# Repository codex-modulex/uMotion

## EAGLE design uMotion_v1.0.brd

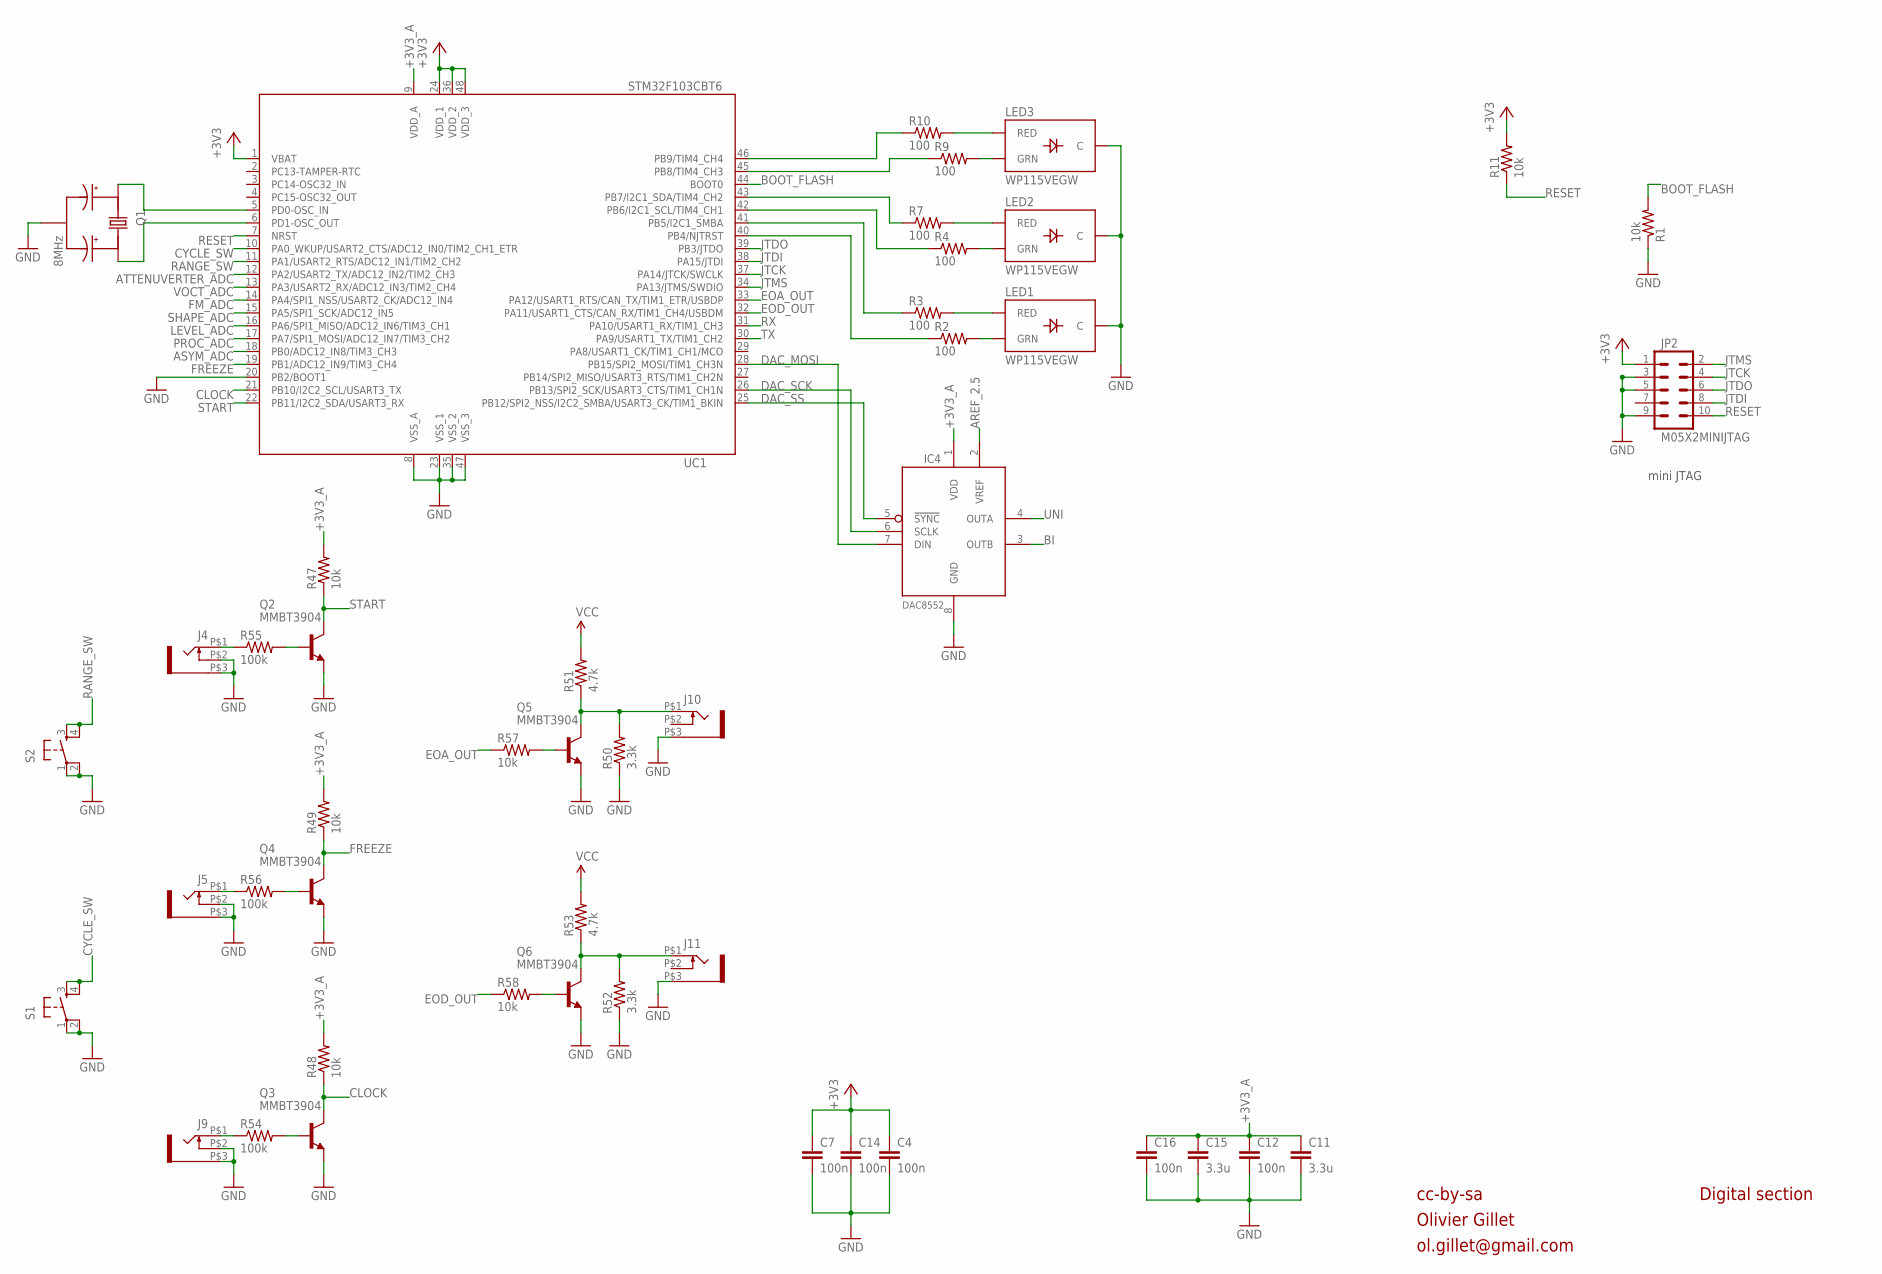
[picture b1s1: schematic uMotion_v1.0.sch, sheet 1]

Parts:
C4, C7, C12, C14, C16: 100n; PARTS_AMAN_RESISTOR_0603
C11, C15: 3.3u; PARTS_AMAN_RESISTOR_0603
IC4: DAC8552; MSOP-8
J4, J5, J9, J10, J11: WQP-PJ301M-12_JACK
JP2: M05X2MINIJTAG; 2X5-1.27
LED1, LED2, LED3: WP115VEGW; LED-BICOLOR-THROUGHHOLE
Q1: 8MHz; INSTRUO_CRYSTAL_SMALLER
Q2, Q3, Q4, Q5, Q6: MMBT3904; SOT23-BEC
R1, R11, R47, R48, R49, R57, R58: 10k; PARTS_AMAN_RESISTOR_0603
R2, R3, R4, R7, R9, R10: 100; PARTS_AMAN_RESISTOR_0603
R50, R52: 3.3k; PARTS_AMAN_RESISTOR_0603
R51, R53: 4.7k; PARTS_AMAN_RESISTOR_0603
R54, R55, R56: 100k; PARTS_AMAN_RESISTOR_0603
S1, S2: TAC_SWITCHPTH; TACTILE-PTH
UC1: STM32F103CBT6; LQFP48

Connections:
+3V3: C4.1, C7.1, C14.1, JP2.1, R11.2, UC1.1 (VBAT), UC1.24 (VDD_1), UC1.36 (VDD_2), UC1.48 (VDD_3); also elsewhere on the board
+3V3_A: C11.1, C12.1, C15.1, C16.1, IC4.1 (VDD), R47.2, R48.2, R49.2, UC1.9 (VDD_A); also elsewhere on the board
AREF_2.5: IC4.2 (VREF); also elsewhere on the board
ASYM_ADC: UC1.18 (PB0/ADC12_IN8/TIM3_CH3); also elsewhere on the board
ATTENUVERTER_ADC: UC1.12 (PA2/USART2_TX/ADC12_IN2/TIM2_CH3); also elsewhere on the board
BI: IC4.3 (OUTB); also elsewhere on the board
BOOT_FLASH: R1.2, UC1.44 (BOOT0)
CLOCK: Q3.C, R48.1, UC1.21 (PB10/I2C2_SCL/USART3_TX)
CYCLE_SW: S1.3, S1.4, UC1.10 (PA0_WKUP/USART2_CTS/ADC12_IN0/TIM2_CH1_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)
DAC_MOSI: IC4.7 (DIN), UC1.28 (PB15/SPI2_MOSI/TIM1_CH3N)
DAC_SCK: IC4.6 (SCLK), UC1.26 (PB13/SPI2_SCK/USART3_CTS/TIM1_CH1N)
DAC_SS: IC4.5 (!SYNC), UC1.25 (PB12/SPI2_NSS/I2C2_SMBA/USART3_CK/TIM1_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)
EOA_OUT: R57.1, UC1.33 (PA12/USART1_RTS/CAN_TX/TIM1_ETR/USBDP)
EOD_OUT: R58.1, UC1.32 (PA11/USART1_CTS/CAN_RX/TIM1_CH4/USBDM)
FM_ADC: UC1.14 (PA4/SPI1_NSS/USART2_CK/ADC12_IN4); also elsewhere on the board
FREEZE: Q4.C, R49.1, UC1.19 (PB1/ADC12_IN9/TIM3_CH4)
GND: C4.2, C7.2, C11.2, C12.2, C14.2, C15.2, C16.2, IC4.8 (GND), J4.P$2 (3), J4.P$3 (1), J5.P$2 (3), J5.P$3 (1), J9.P$2 (3), J9.P$3 (1), J10.P$3 (1), J11.P$3 (1), JP2.3, JP2.5, JP2.9, LED1.2 (C), LED2.2 (C), LED3.2 (C), Q1.GND, Q2.E, Q3.E, Q4.E, Q5.E, Q6.E, R1.1, R50.1, R52.1, S1.1, S1.2, S2.1, S2.2, UC1.8 (VSS_A), UC1.20 (PB2/BOOT1), UC1.23 (VSS_1), UC1.35 (VSS_2), UC1.47 (VSS_3); also elsewhere on the board
JTCK: JP2.4, UC1.37 (PA14/JTCK/SWCLK)
JTDI: JP2.8, UC1.38 (PA15/JTDI)
JTDO: JP2.6, UC1.39 (PB3/JTDO)
JTMS: JP2.2, UC1.34 (PA13/JTMS/SWDIO)
LEVEL_ADC: UC1.16 (PA6/SPI1_MISO/ADC12_IN6/TIM3_CH1); also elsewhere on the board
unnamed: Q1.X2, UC1.6 (PD1-OSC_OUT)
unnamed: Q1.X1, UC1.5 (PD0-OSC_IN)
unnamed: J5.P$1 (2), R56.1
unnamed: Q4.B, R56.2
unnamed: J9.P$1 (2), R54.1
unnamed: Q3.B, R54.2
unnamed: Q6.B, R58.2
unnamed: J11.P$1 (2), Q6.C, R52.2, R53.1
unnamed: LED3.3 (RED), R10.2
unnamed: LED3.1 (GRN), R9.2
unnamed: LED2.3 (RED), R7.2
unnamed: LED2.1 (GRN), R4.2
unnamed: LED1.3 (RED), R3.2
unnamed: LED1.1 (GRN), R2.2
unnamed: R10.1, UC1.46 (PB9/TIM4_CH4)
unnamed: R9.1, UC1.45 (PB8/TIM4_CH3)
unnamed: R7.1, UC1.43 (PB7/I2C1_SDA/TIM4_CH2)
unnamed: R4.1, UC1.42 (PB6/I2C1_SCL/TIM4_CH1)
unnamed: R3.1, UC1.41 (PB5/I2C1_SMBA)
unnamed: R2.1, UC1.40 (PB4/NJTRST)
unnamed: J10.P$1 (2), Q5.C, R50.2, R51.1
unnamed: Q5.B, R57.2
unnamed: J4.P$1 (2), R55.1
unnamed: Q2.B, R55.2
PROC_ADC: UC1.17 (PA7/SPI1_MOSI/ADC12_IN7/TIM3_CH2); also elsewhere on the board
RANGE_SW: S2.3, S2.4, UC1.11 (PA1/USART2_RTS/ADC12_IN1/TIM2_CH2)
RESET: JP2.10, R11.1, UC1.7 (NRST)
RX: UC1.31 (PA10/USART1_RX/TIM1_CH3)
SHAPE_ADC: UC1.15 (PA5/SPI1_SCK/ADC12_IN5); also elsewhere on the board
START: Q2.C, R47.1, UC1.22 (PB11/I2C2_SDA/USART3_RX)
TX: UC1.30 (PA9/USART1_TX/TIM1_CH2)
UNI: IC4.4 (OUTA); also elsewhere on the board
VCC: R51.2, R53.2; also elsewhere on the board
VOCT_ADC: UC1.13 (PA3/USART2_RX/ADC12_IN3/TIM2_CH4); also elsewhere on the board

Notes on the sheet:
cc-by-sa
Olivier Gillet
ol.gillet@gmail.com
Digital section
mini JTAG

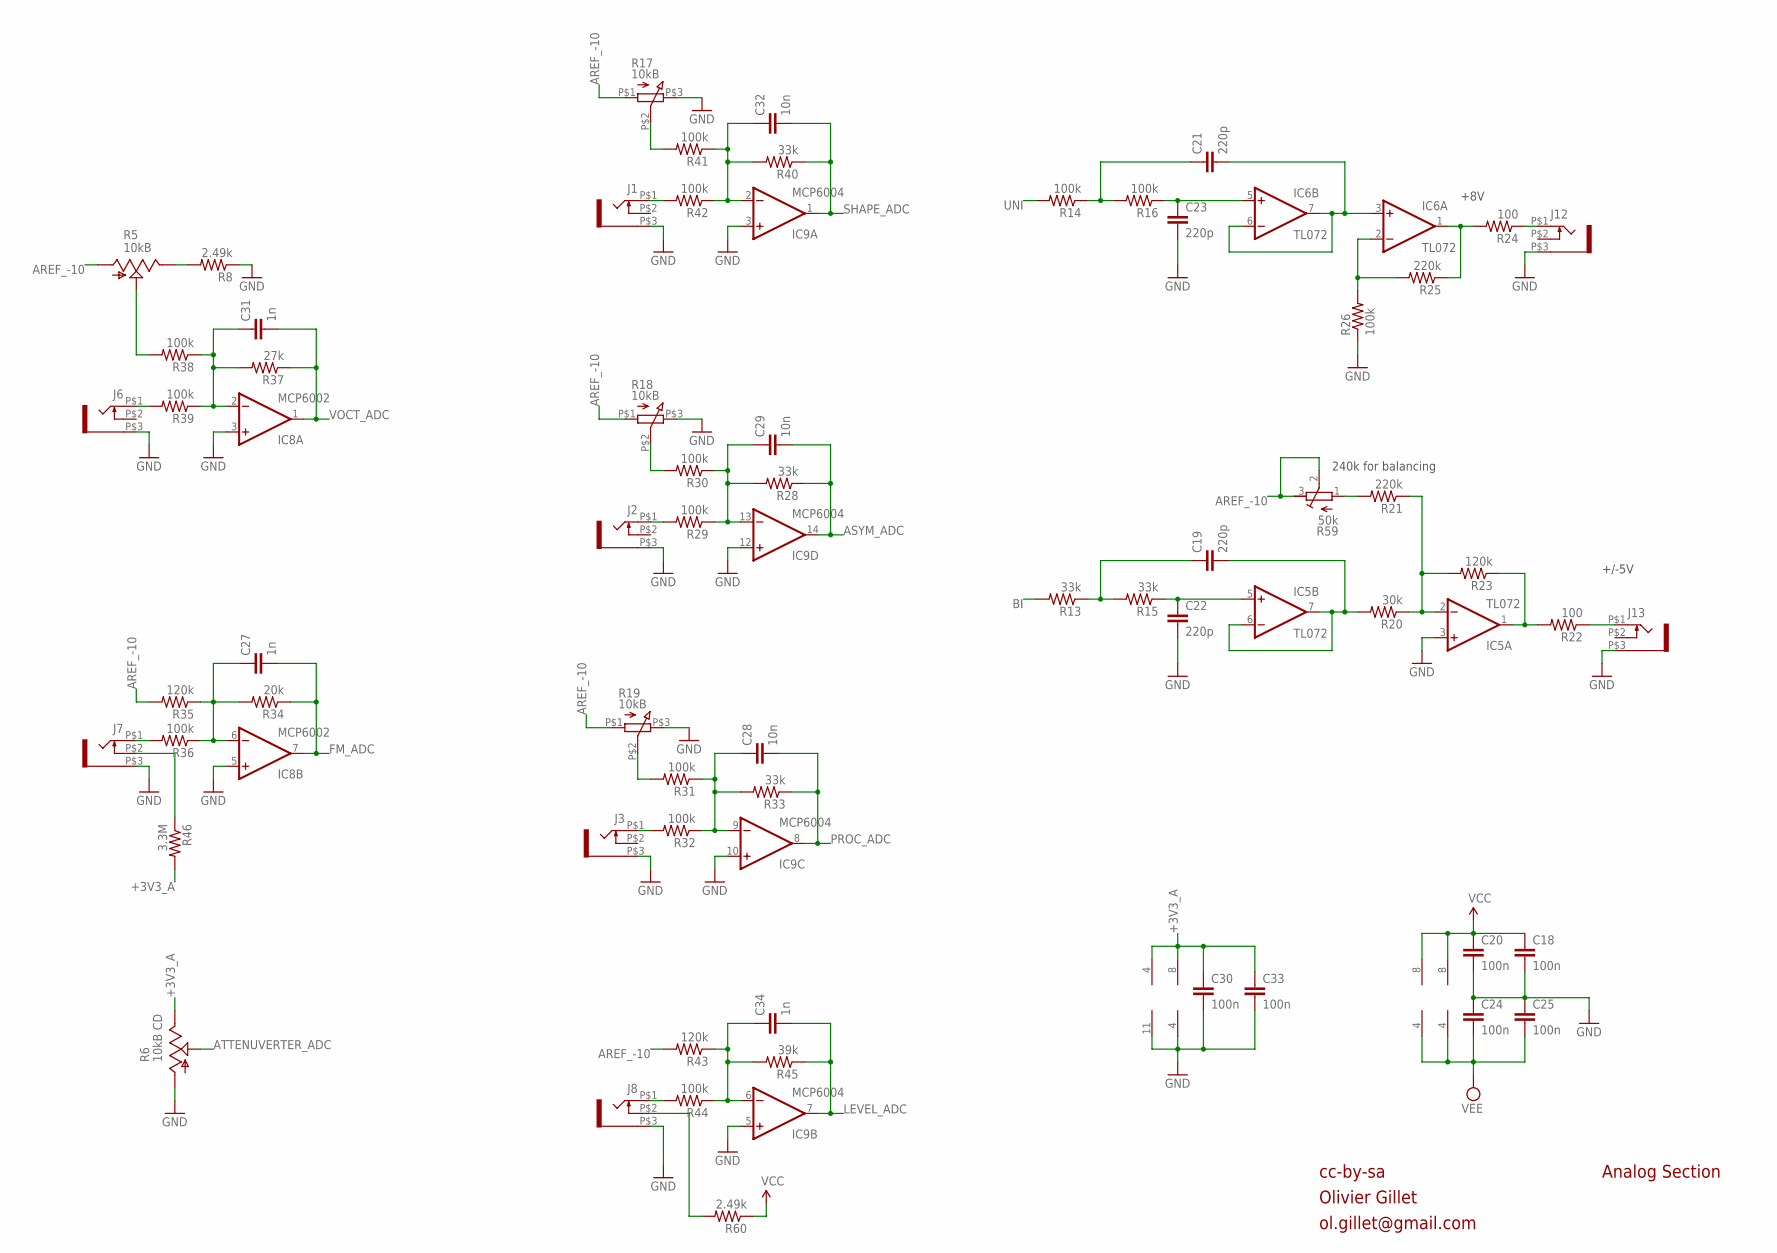
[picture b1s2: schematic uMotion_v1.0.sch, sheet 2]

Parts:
C18, C20, C24, C25, C30, C33: 100n; PARTS_AMAN_RESISTOR_0603
C19, C21, C22, C23: 220p; PARTS_AMAN_RESISTOR_0603
C27, C31, C34: 1n; PARTS_AMAN_RESISTOR_0603
C28, C29, C32: 10n; PARTS_AMAN_RESISTOR_0603
IC5, IC6: TL072; SO08
IC8: MCP6002; SO08
IC9: MCP6004; SO14
J1, J2, J3, J6, J7, J8, J12, J13: WQP-PJ301M-12_JACK
R5: 10kB; ALPS_POT_VERTICAL_PS
R6: 10kB CD; ALPS_POT_VERTICAL_PS
R8: 2.49k; PARTS_AMAN_RESISTOR_0603
R13, R15, R28, R33, R40: 33k; PARTS_AMAN_RESISTOR_0603
R14, R16, R26, R29, R30, R31, R32, R36, R38, R39, R41, R42, R44: 100k; PARTS_AMAN_RESISTOR_0603
R17, R18, R19: 10kB; INSTRUO_Q-POT2
R20: 30k; PARTS_AMAN_RESISTOR_0603
R21, R25: 220k; PARTS_AMAN_RESISTOR_0603
R22, R24: 100; PARTS_AMAN_RESISTOR_0603
R23, R35, R43: 120k; PARTS_AMAN_RESISTOR_0603
R34: 20k; PARTS_AMAN_RESISTOR_0603
R37: 27k; PARTS_AMAN_RESISTOR_0603
R45: 39k; PARTS_AMAN_RESISTOR_0603
R46: 3.3M; PARTS_AMAN_RESISTOR_0603
R59: 50k; RTRIM3296X
R60: 2.49k; R0805

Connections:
+3V3_A: C30.1, C33.1, IC8.8 (V+), IC9.4 (V+), R6.P$1 (E), R46.2; also elsewhere on the board
AREF_-10: R5.P$3 (A), R17.P$1 (1), R18.P$1 (1), R19.P$1 (1), R35.2, R43.2, R59.2 (S), R59.3 (A); also elsewhere on the board
ASYM_ADC: C29.2, IC9.14 (OUT), R28.1; also elsewhere on the board
ATTENUVERTER_ADC: R6.P$2 (S); also elsewhere on the board
BI: R13.2; also elsewhere on the board
BI_OUT: IC5.1 (OUT), R22.2, R23.1
FM_ADC: C27.2, IC8.7 (OUT), R34.1; also elsewhere on the board
F_CV: IC5.2 (-IN), R20.1, R21.1, R23.2
GND: C18.2, C20.2, C22.2, C23.2, C24.1, C25.1, C30.2, C33.2, IC5.3 (+IN), IC8.3 (+IN), IC8.4 (V-), IC8.5 (+IN), IC9.3 (+IN), IC9.5 (+IN), IC9.10 (+IN), IC9.11 (V-), IC9.12 (+IN), J1.P$3 (1), J2.P$3 (1), J3.P$3 (1), J6.P$3 (1), J7.P$3 (1), J8.P$3 (1), J12.P$3 (1), J13.P$3 (1), R6.P$3 (A), R8.1, R17.P$3 (3), R18.P$3 (3), R19.P$3 (3), R26.1; also elsewhere on the board
LEVEL_ADC: C34.2, IC9.7 (OUT), R45.1; also elsewhere on the board
unnamed: J1.P$1 (2), R42.2
unnamed: C32.1, IC9.2 (-IN), R40.2, R41.1, R42.1
unnamed: R17.P$2 (2), R41.2
unnamed: J2.P$1 (2), R29.2
unnamed: C29.1, IC9.13 (-IN), R28.2, R29.1, R30.1
unnamed: J7.P$2 (3), R46.1
unnamed: R18.P$2 (2), R30.2
unnamed: J3.P$1 (2), R32.2
unnamed: C28.1, IC9.9 (-IN), R31.1, R32.1, R33.2
unnamed: R19.P$2 (2), R31.2
unnamed: J8.P$1 (2), R44.2
unnamed: C34.1, IC9.6 (-IN), R43.1, R44.1, R45.2
unnamed: J6.P$1 (2), R39.2
unnamed: C31.1, IC8.2 (-IN), R37.2, R38.1, R39.1
unnamed: R5.P$2 (S), R38.2
unnamed: J13.P$1 (2), R22.1
unnamed: R5.P$1 (E), R8.2
unnamed: J7.P$1 (2), R36.2
unnamed: C27.1, IC8.6 (-IN), R34.2, R35.1, R36.1
unnamed: R21.2, R59.1 (E)
unnamed: IC6.2 (-IN), R25.2, R26.2
unnamed: C19.2, IC5.6 (-IN), IC5.7 (OUT), R20.2
unnamed: C22.1, IC5.5 (+IN), R15.1
unnamed: C19.1, R13.1, R15.2
unnamed: IC6.1 (OUT), R24.2, R25.1
unnamed: J8.P$2 (3), R60.2
unnamed: C21.2, IC6.3 (+IN), IC6.6 (-IN), IC6.7 (OUT)
unnamed: C23.1, IC6.5 (+IN), R16.1
unnamed: C21.1, R14.1, R16.2
PROC_ADC: C28.2, IC9.8 (OUT), R33.1; also elsewhere on the board
SHAPE_ADC: C32.2, IC9.1 (OUT), R40.1; also elsewhere on the board
UNI: R14.2; also elsewhere on the board
UNI_OUT: J12.P$1 (2), R24.1
VCC: C18.1, C20.1, IC5.8 (V+), IC6.8 (V+), R60.1; also elsewhere on the board
VEE: C24.2, C25.2, IC5.4 (V-), IC6.4 (V-); also elsewhere on the board
VOCT_ADC: C31.2, IC8.1 (OUT), R37.1; also elsewhere on the board

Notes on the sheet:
cc-by-sa
Olivier Gillet
ol.gillet@gmail.com
Analog Section
+8V
+/-5V
240k for balancing

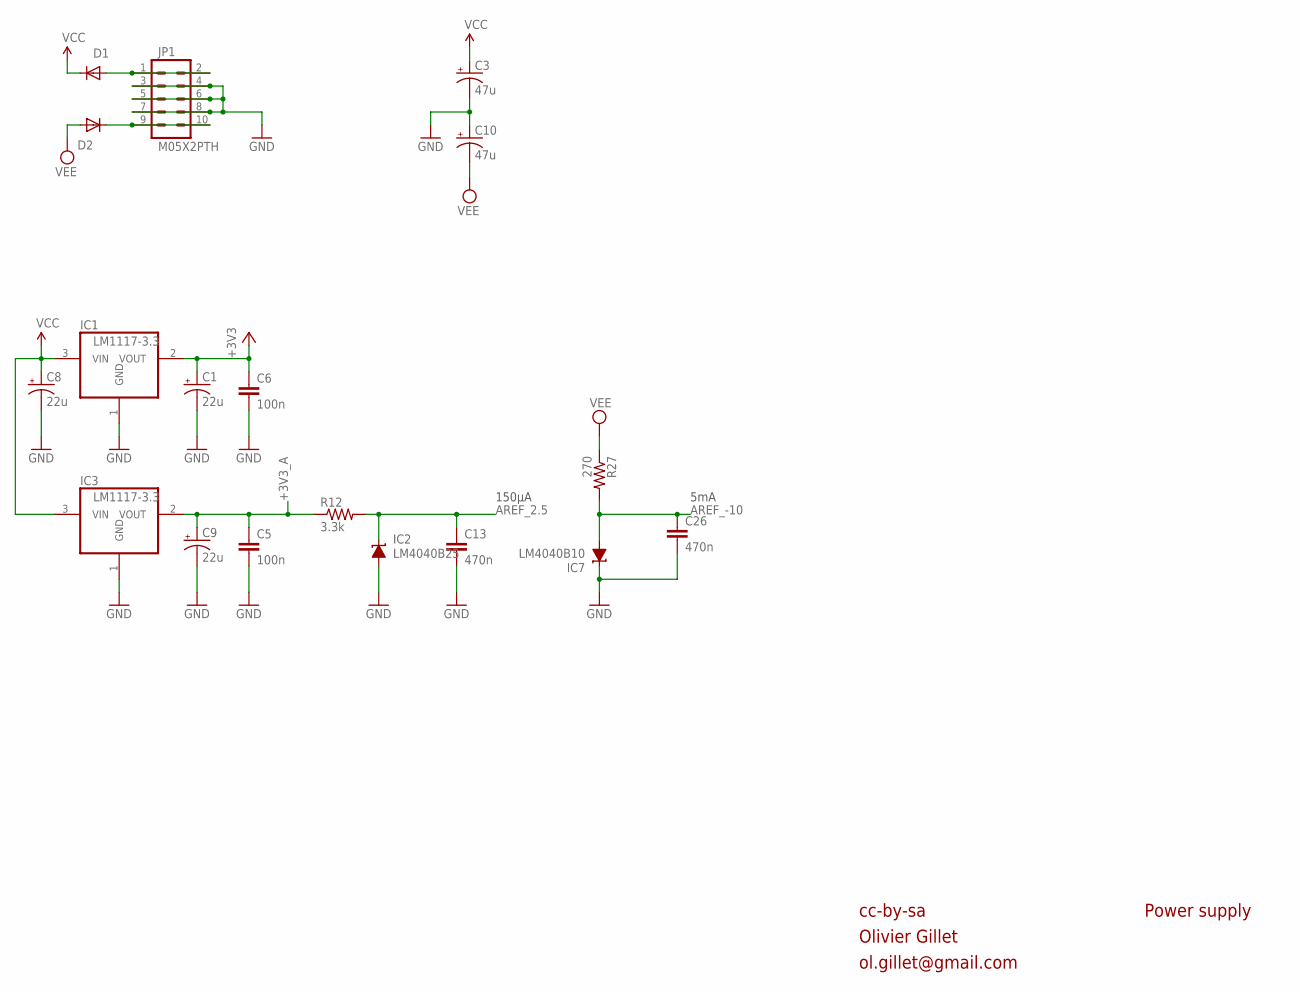
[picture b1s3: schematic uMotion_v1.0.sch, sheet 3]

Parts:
C1, C8, C9: 22u; PANASONIC_C
C3, C10: 47u; PANASONIC_D
C5, C6: 100n; PARTS_AMAN_RESISTOR_0603
C13, C26: 470n; PARTS_AMAN_RESISTOR_0603
D1, D2: 1N5819HW; SOD123
IC1, IC3: LM1117-3.3; SOT223
IC2: LM4040B25; DBZ_R-PDSO-G3
IC7: LM4040B10; DBZ_R-PDSO-G3
JP1: M05X2PTH; AVR_ICSP
R12: 3.3k; PARTS_AMAN_RESISTOR_0603
R27: 270; PARTS_AMAN_RESISTOR_0603

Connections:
+3V3: C1.+, C6.1, IC1.2 (VOUT); also elsewhere on the board
+3V3_A: C5.1, C9.+, IC3.2 (VOUT), R12.1; also elsewhere on the board
AREF_2.5: C13.1, IC2.1 (C), R12.2; also elsewhere on the board
AREF_-10: C26.1, IC7.2 (A), R27.2; also elsewhere on the board
GND: C1.-, C3.-, C5.2, C6.2, C8.-, C9.-, C10.+, C13.2, C26.2, IC1.1 (GND), IC2.2 (A), IC3.1 (GND), IC7.1 (C), JP1.3, JP1.4, JP1.5, JP1.6, JP1.7, JP1.8; also elsewhere on the board
unnamed: D1.A, JP1.1, JP1.2
unnamed: D2.C, JP1.9, JP1.10
VCC: C3.+, C8.+, D1.C, IC1.3 (VIN), IC3.3 (VIN); also elsewhere on the board
VEE: C10.-, D2.A, R27.1; also elsewhere on the board

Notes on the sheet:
cc-by-sa
Olivier Gillet
ol.gillet@gmail.com
Power supply
5mA
150µA

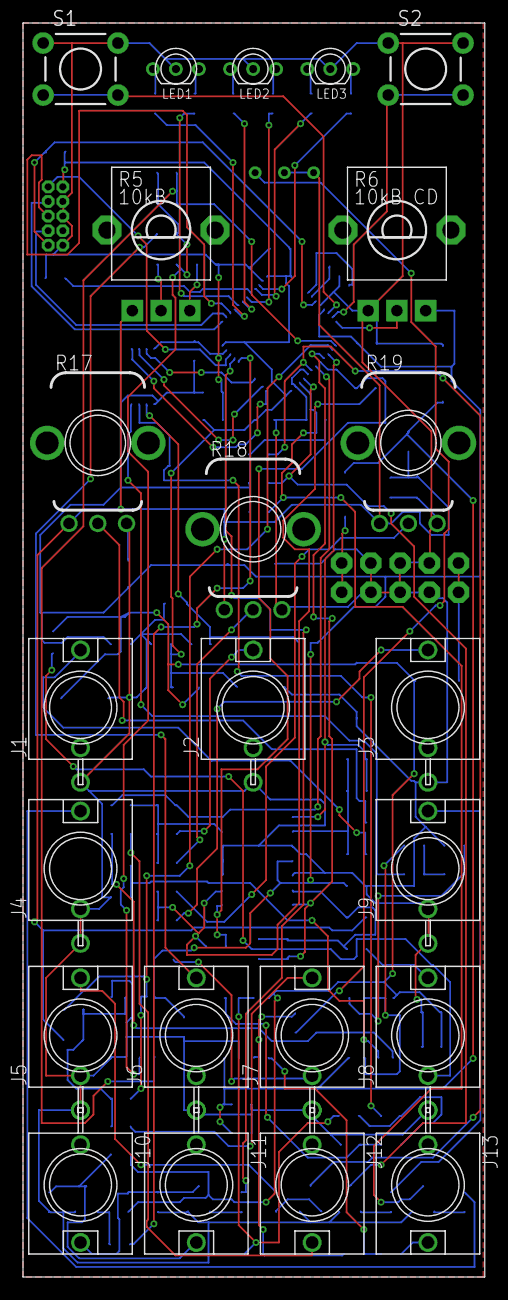
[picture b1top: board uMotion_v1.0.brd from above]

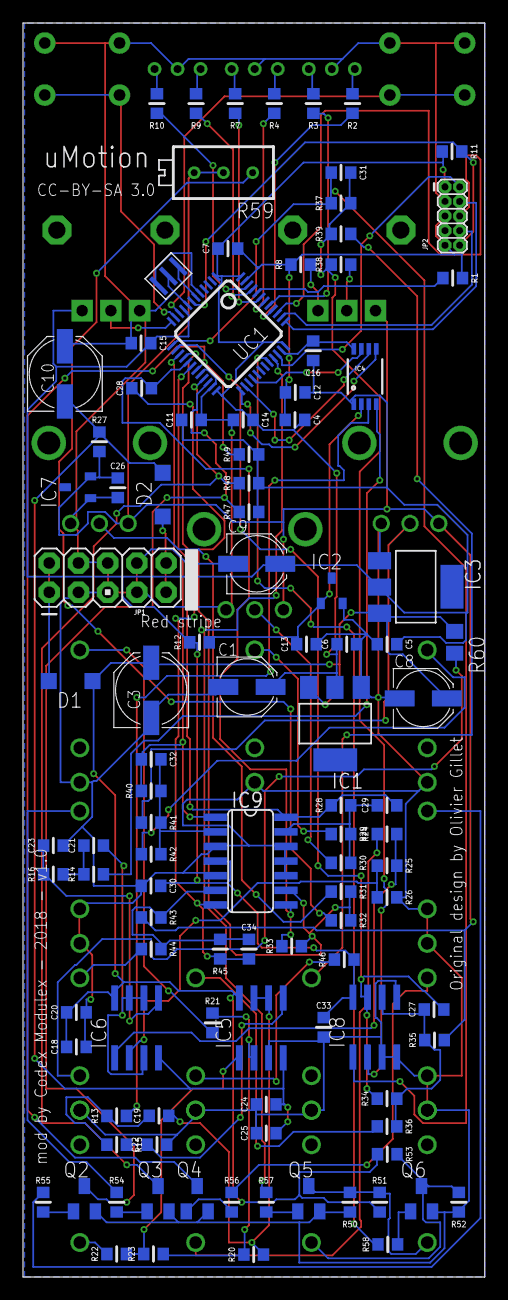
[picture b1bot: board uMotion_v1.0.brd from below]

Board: 2 copper layers, 40.1 x 109.0 mm, 130 parts (107 on the bottom side), 90 nets.

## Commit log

2018-12-11 uMotion files

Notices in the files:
uMotion_v1.0.brd:
CC-BY-SA 3.0
